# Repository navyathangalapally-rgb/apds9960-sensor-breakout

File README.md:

# APDS-9960 color Sensor PCB

This project involves the design and development of a custom PCB integrating an STM32 microcontroller with the APDS-9960 sensor for gesture, proximity, and color detection.

It was developed as part of laboratory work, focusing on sensor interfacing and embedded hardware design.

##  Overview

The goal of this project was to design a compact and reliable hardware system capable of interfacing with a multi-function sensor over I2C.

The system includes:
- STM32F103C8T6 microcontroller
- APDS-9960 gesture and color sensor
- Power regulation and USB interface

## How it Works

1. The APDS-9960 sensor detects gestures, proximity, and color data  
2. Communication is established via I2C protocol  
3. The STM32 processes the incoming sensor data  
4. The system can be extended for gesture-based control applications  

## Hardware Design

- Designed using **KiCad**
- Implemented stable **3.3V power supply**
- Proper decoupling capacitors added for noise reduction
- Clean PCB layout to ensure reliable signal routing

## Project Visuals

### 🔹 3D PCB Render

### 🔹 Full Schematic

### 🔹 Sensor Interface (APDS-9960)

### 🔹 PCB Layout

## Tech Stack

- **Design Tool:** KiCad  
- **Microcontroller:** STM32F103C8T6  
- **Sensor:** APDS-9960  
- **Communication:** I2C  
- **Power:** 3.3V via Micro-USB  

## Repository Contents

- KiCad design files (`.kicad_pcb`, `.kicad_sch`, `.kicad_pro`)  
- PCB layout and schematic images  
- 3D model files  

## My Contribution

- Designed the schematic and PCB layout  
- Integrated STM32 with APDS-9960 sensor  
- Ensured stable power and proper signal routing  
- Validated the hardware design  

## Future Improvements

- Firmware implementation for real-time gesture recognition  
- Integration with robotics or automation systems  
- ROS-based sensor data publishing (future scope)

## Timeline

Developed as part of laboratory work (Dec 2024)

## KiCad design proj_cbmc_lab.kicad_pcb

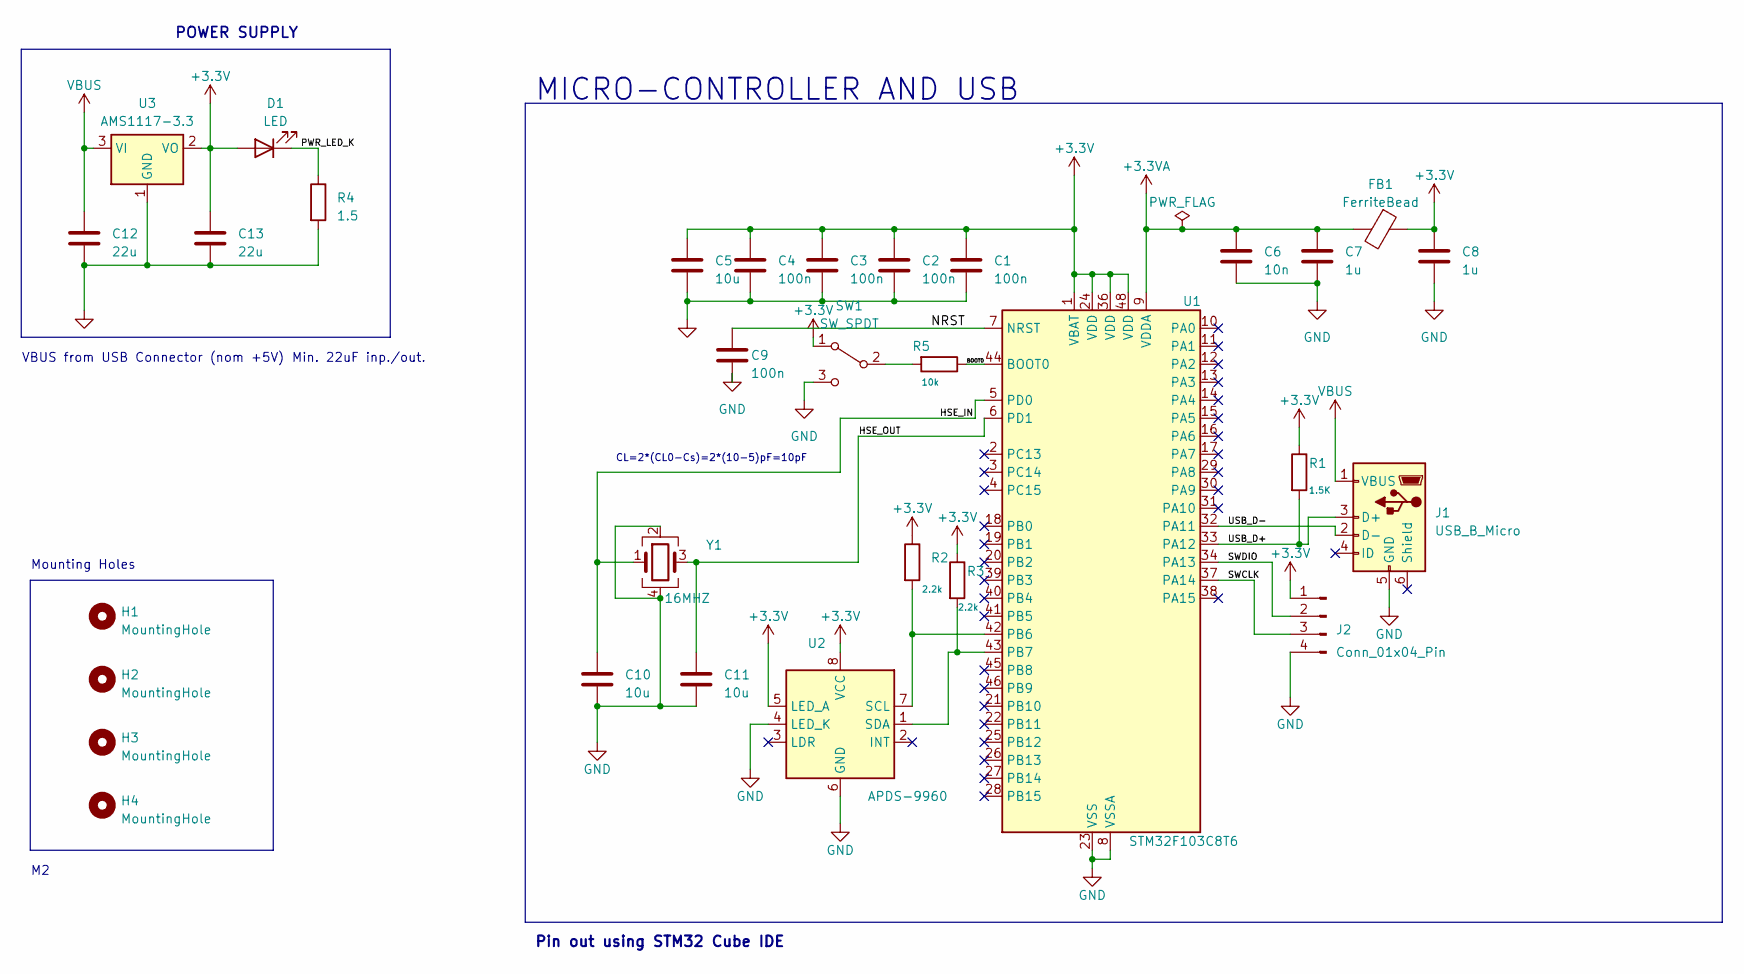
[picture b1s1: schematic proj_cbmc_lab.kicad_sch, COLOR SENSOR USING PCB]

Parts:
C1, C2, C3, C4, C9: 100n; C_0402_1005Metric
C5, C10, C11: 10u; C_0603_1608Metric
C6: 10n; C_0402_1005Metric
C7, C8: 1u; C_0402_1005Metric
C12, C13: 22u; C_0805_2012Metric
D1: LED; LED_0603_1608Metric
FB1: FerriteBead; L_0603_1608Metric
H1, H2, H3, H4: MountingHole; MountingHole_2.2mm_M2
J1: USB_B_Micro; USB_Micro-B_Wuerth_629105150521
J2: Conn_01x04_Pin; PinHeader_1x04_P2.54mm_Vertical
R1: 1.5K; R_0402_1005Metric
R2, R3: 2.2k; R_0402_1005Metric
R4: 1.5; R_0402_1005Metric
R5: 10k; R_0402_1005Metric
SW1: SW_SPDT; SW_SP3T_PCM13
U1: STM32F103C8T6; LQFP-48_7x7mm_P0.5mm
U2: APDS-9960; Avago_APDS-9960
U3: AMS1117-3.3; SOT-223-3_TabPin2
Y1: 16MHZ; Crystal_SMD_3225-4Pin_3.2x2.5mm

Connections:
+3.3V: C1.1, C2.1, C3.1, C4.1, C5.1, C8.1, C13.1, D1.2 (A), FB1.1, J2.1, R1.1, R2.1, R3.1, SW1.1 (A), U1.1 (VBAT), U1.24 (VDD), U1.36 (VDD), U1.48 (VDD), U2.5 (LED_A), U2.8 (VCC), U3.2 (VO)
+3.3VA: C6.1, C7.1, FB1.2, U1.9 (VDDA)
/BOOT0: R5.1, U1.44 (BOOT0)
/HSE_IN: C10.1, U1.5 (PD0), Y1.1
/HSE_OUT: C11.1, U1.6 (PD1), Y1.3
/NRST: C9.1, U1.7 (NRST)
/PWR_LED_K: D1.1 (K), R4.1
/SWCLK: J2.3, U1.37 (PA14)
/SWDIO: J2.2, U1.34 (PA13)
/USB_D+: J1.3 (D+), R1.2, U1.33 (PA12)
/USB_D-: J1.2 (D-), U1.32 (PA11)
GND: C1.2, C2.2, C3.2, C4.2, C5.2, C6.2, C7.2, C8.2, C9.2, C10.2, C11.2, C12.2, C13.2, J1.5 (GND), J1.6 (Shield), J2.4, R4.2, SW1.3 (C), U1.8 (VSSA), U1.23 (VSS), U1.35 (VSS), U1.47 (VSS), U2.4 (LED_K), U2.6 (GND), U3.1 (GND), Y1.2, Y1.4
unnamed: R5.2, SW1.2 (B)
unnamed: R2.2, U1.42 (PB6), U2.7 (SCL)
unnamed: R3.2, U1.43 (PB7), U2.1 (SDA)
VBUS: C12.1, J1.1 (VBUS), U3.3 (VI)

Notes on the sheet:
Pin out using STM32 Cube IDE
Mounting Holes
POWER SUPPLY
Min. 22uF inp./out.
VBUS from USB Connector (nom +5V)
MICRO-CONTROLLER AND USB
CL=2*(CL0-Cs)=2*(10-5)pF=10pF

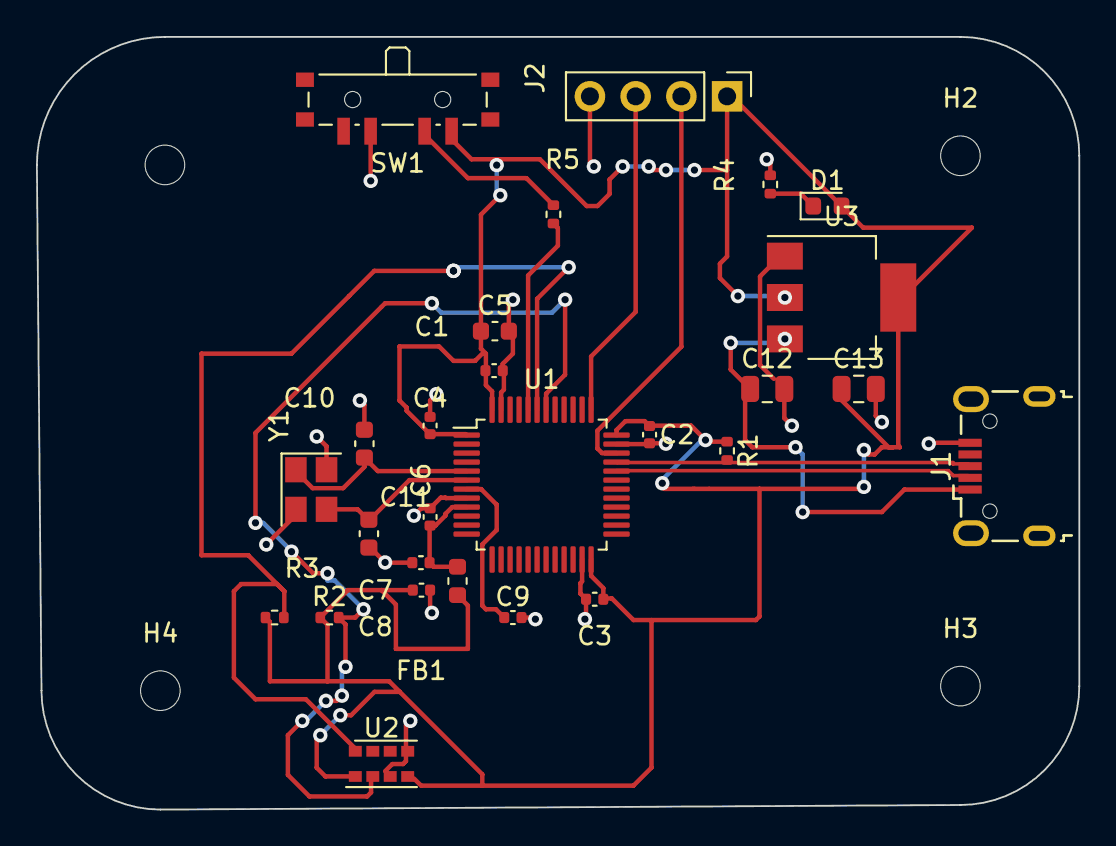
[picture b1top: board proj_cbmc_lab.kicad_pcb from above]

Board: 2 copper layers, 57.9 x 42.9 mm, 31 parts (0 on the bottom side), 16 nets.

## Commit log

2026-05-02 Add files via upload
    Add schematic and PCB renders to the project.
2026-05-05 Add MIT License
2026-05-06 Revise README with project overview and visuals
    KiCad-based PCB-Design for APDS9960 color sensor module.
2026-05-06 Fix formatting by removing empty line in README
    Removed an empty line for better formatting.
